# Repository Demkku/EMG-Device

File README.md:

Everything done, everything up to date and project presented.

final presentation:
https://docs.google.com/presentation/d/1xxOuLbYDE3mbfAP0H2NyMZXC_jU_autwXX0Ozza_mss/edit?usp=sharing

repository:
https://github.com/Demkku/EMG-Device

diary:
https://demkku.github.io/EMG-Device/

## Summary report

click [here]({{ site.baseurl }}/assets/EMG summary report.pdf) to download the summary report PDF with pictures and links
Note! link only available when browsing github pages and the link doesn't seem to work with Edge Browser

Our final concept was to measure heart rate using voltage sensors that have been amplified and filtered using operational amplifiers. Then the heart rate peak is detected with Arduino and the time difference between the peaks is measured and converted for a servo. Then the servo moves a needle on a measuring table to display the heart rate.

Our project consists of 4 elements: a circuit board and a case for it, a measuring table and software to read sensor data and convert into readable data and software to control a servo for the measuring table. 

Johannes designed the circuit board using KiCad. Voltage -sensors didn’t have strong enough signal, so in order to use it properly the signal had to be amplified and filtered using operational amplifiers. The voltage difference in the order of 1mV is measured across the chest with EKG electrodes, +, - and ground. The signal to an instrumental operational amplifier, where common mode noise is rejected, and the signal is amplified. Next, the signal goes through low and high pass filters. After filtering is further amplification and full wave rectification. Last, one more amplifier and then the signal goes to the ADC of ATMEGA328p. 

The case was designed by using Blender. Blender isn’t quite the best software in designing real life objects, but to create a simple and aesthetically nice case wasn’t a problem. The case was designed around the project images exported from Kicad. Some approximation by eye had to be made with components and they were pretty much correct. Only the size of the PCB would have gone terribly wrong if only the Kicad images were followed. The case was finally printed with Fortus 380mc printer. The result was fair, only the bottom was so thin that it cracked a little.

The measuring table was designed with Blender, from which the vector file was imported to Inkscape.
From Inkscape the vector file was exported as a pdf and then printed using a laser cutter out of plywood. The first cut table was too thick, and the servo couldn’t be put through. The arrow needed a hole for the screw, too. That’s why the table was cut again, and it turned out without problems. The servo was glued on the backside of the table.

The software was done on Arduino IDE platform. We programmed our code to ATMEGA328p microcontroller using Arduino UNO. The programs purpose was to measure the time difference between every heartbeat and calculate how many times the heart beats in a minute. EKG -sensors had a triangle wave that measured voltage of the heartbeat and it had some noise in it. To get reliable data we had to calculate the time difference between every peak of the voltage signal and not take the noise into account. We made the program to measure only the rising side of the wave and its maximum voltage. That way we got the most reliable data. Then we had to program a correct angle to a servo to display the heartrate on a measuring table.

Lessons learned 

We learned a lot in this project. We learned to use different software like KiCad, Blender, GitHub and Inkscape. We learned that one should always make a second version of the hardware design if any problems would rise. We learned how to use operational amplifiers in practice and how to compare different components to get the best one for its use. We also learned to watch carefully that everything gets correctly imported other software like all of our parts in the circuit board design didn’t get correctly imported to the drilling machine because we used KiCad as our design system.

We learned a good lesson in time management. It would be a lot better to divide the work of the project to entire period so there wouldn’t be such a rush at the end of the period to get everything done.

Our recommendation to others doing the same project is to take your time designing every element of the project carefully so everything goes smoothly when you start building up the project. This project can be a bit difficult so it would be better done in your on pace and not in an introductory course like Principles of digital fabrication.

Feedback to course responsibles

 The course was nice. It was good change for our usual courses that are heavily theoretic besed. It helped us to learn new things to designour projects so the course was also quite usefull.

## W19

On monday the case is printed, also
project software created and completed as it is very simple. 
The case slightly cracked during removal from the printer.

With the completetion of SW with Aruino IDE and receiving of the mesuring electrodes on the last minute
PROJECT COMPLETED!!!

the complete project:

testing after pads finally received:

The code:

## W18

Testing software created. Extensive testing and simulation done. 
See baseband testing report and oscilloscope pictures.

final output to ADC on simulation, massive hf noise:

Component values changed and filtering added

## W17

The remaining components soldered and measurements taken to the case.
During the soldering, some missing traces noticed, but fixed with jump wires.
Traces missing on the layout.

EKG electrodes ordered from Medkit.

Modeling of the case started with blender.
Also, modeling of the measuring table started with blender.

## W16

Midterm meeting

Later on the week, components received and first soldered.

## W15

The idea maybe changed to a heart rate sensor, which can be measured with the same circuit. 
Will be tested when components received, probably on W16 or 17

V2 board Milled with Success!!!

On the left first try, on the right the V2 board

Components ordered from Mouser.

Design for an enclosure started, will be 3D printed.

## W14

Layout V1 started and completed:

BOM completed.

V1 board milled. The board failed with board width at 0.4mm and uneven board at milling machine.
As a result wire width doubled to 0.8mm wherever possible.

## W13

After brainstorming requrements set

Kicad schematics started:

Kicad schematics done after a lot of reading about op amps:

## W12

The repositery and site created

## Start of the project:

Introductory report, EMG-Device

521159P Principles of Digital Fabrication 
DIGIFAB10 

The idea is to build a device that can measure EMG signal. EMG signals are created when muscles are used, and nerve impulses are sent. Impulses create a potential difference in the order of 1-10mV which is amplified, filtered and read with an Arduino. To meet course requirements an enclosure will be 3D printed and something laser cut. We arrived at the idea of an EMG device as a combination interest to the subject of bio signals, the challenge and courses about op amps are running in parallel with this course, so we can use in practice what we have learned. 

Other project that we thought of was an Arduino tank that could locate WIFI signal sources, but this would have been very software heavy, and because we are EE students, we wanted to put emphasis on hardware. Also locating sources turns out to be very hard. Our back up plan is an EKG device, which instead of 3 measuring lanes, uses only one.

BOM:
QTY	Component type	Package	Source	Price(eur)	URL

10	0.1uF capacitor	1206	Electronics club	0	

1	1uF capacitor	0603	Johannes	0	

1	12nF capacitor	0603	Johannes	0	

1	20nF capacitor	0603	Johannes	0	

3	47uF capacitor	5x5mm	Johannes	0	

1	47pF capacitor	0603	Johannes	0	

2	10uF tant. Cap.	1206?	Electronics club	0	

2	SMD LED	0603	Johannes	0	

2	1N4148W-F, SMD diode	SOD-123	Mouser	0,3	https://www.mouser.fi/ProductDetail/Diodes-Incorporated/1N4148W-7-F?qs=sGAEpiMZZMvilazpv%252bFqvbevgE8TPEOt

1	3 pin header	male 100mil header	Electronics club	0	

1	3 screw terminal	5mm terminal	Johannes	0	

1	2 screw terminal	5mm terminal	Johannes	0	

2	1MOhm resistor	0603?	Electronics club/Johannes	0	

1	470 Ohm resistor	0603	Johannes	0	

2	82kOhm resistor	0603	Johannes	0	

2	120kOhm resistor	0603	Johannes	0	

5	10kOhm resistor	0603	Johannes	0	

1	4,7kOhm resistor	0603	Johannes	0	

5	1kOhm resistor	0603	Johannes	0	

1	0 Ohm resistor	0603	Johannes	0	

1	15kOhm resistor	0603	Johannes	0	

1	100kOhm resistor	0603	Johannes	0	

2	DIP8 socket	DIP8	Johannes	0	

1	DIP14 socket	DIP14	Johannes	0	

1	DIP28 socket	DIP28	Johannes	0	

1	MAX1720 charge pump	TSOP-6	Mouser	0,58	https://www.mouser.fi/ProductDetail/ON-Semiconductor/MAX1720EUTG?qs=sGAEpiMZZMtitjHzVIkrqdfdkrf0Qy0Qzg%252b1DRXikVE%3d

1	HC-05 BT unit	custom	Johannes	0	

1	INA121PA inst. amp.	DIP8	Mouser	4,94	https://www.mouser.fi/ProductDetail/Texas-Instruments/INA121PA?qs=sGAEpiMZZMsE1dKaA2ImUPh%2fgv48%2feoeALcGDSe487k%3d

1	TL072IP op. Amp.	DIP8	Mouser	0,56	https://www.mouser.fi/ProductDetail/Texas-Instruments/TL072IP?qs=5BZzbFV4k2v7IBrcArRPQw==

1	LM324N	DIP14	Mouser	0,43	https://www.mouser.fi/ProductDetail/Texas-Instruments/LM324N?qs=sGAEpiMZZMtCHixnSjNA6Araa3jp4DVB37ZJv3RooEc%3d

1	ATMega 328p	DIP28	Electronics club	0	

1	LM1117 3.3V regulator	TO252	Electronics club	0	

8	button things	button	Johannes	0	

50	Electrodes, 34mm	button	Medkit.fi	14,26	https://www.medkit.fi/ambu-blue-sensor-m-oo-s?___store=finland&nosto=frontpage-nosto-1

## Welcome to GitHub Pages

You can use the [editor on GitHub](https://github.com/Demkku/EMG-Device/edit/master/README.md) to maintain and preview the content for your website in Markdown files.

Whenever you commit to this repository, GitHub Pages will run [Jekyll](https://jekyllrb.com/) to rebuild the pages in your site, from the content in your Markdown files.

### Markdown

Markdown is a lightweight and easy-to-use syntax for styling your writing. It includes conventions for

```markdown
Syntax highlighted code block

# Header 1
## Header 2
### Header 3

- Bulleted
- List

1. Numbered
2. List

**Bold** and _Italic_ and `Code` text

[Link](url) and 
```

For more details see [GitHub Flavored Markdown](https://guides.github.com/features/mastering-markdown/).

### Jekyll Themes

Your Pages site will use the layout and styles from the Jekyll theme you have selected in your [repository settings](https://github.com/Demkku/EMG-Device/settings). The name of this theme is saved in the Jekyll `_config.yml` configuration file.

### Support or Contact

Having trouble with Pages? Check out our [documentation](https://help.github.com/categories/github-pages-basics/) or [contact support](https://github.com/contact) and we’ll help you sort it out.

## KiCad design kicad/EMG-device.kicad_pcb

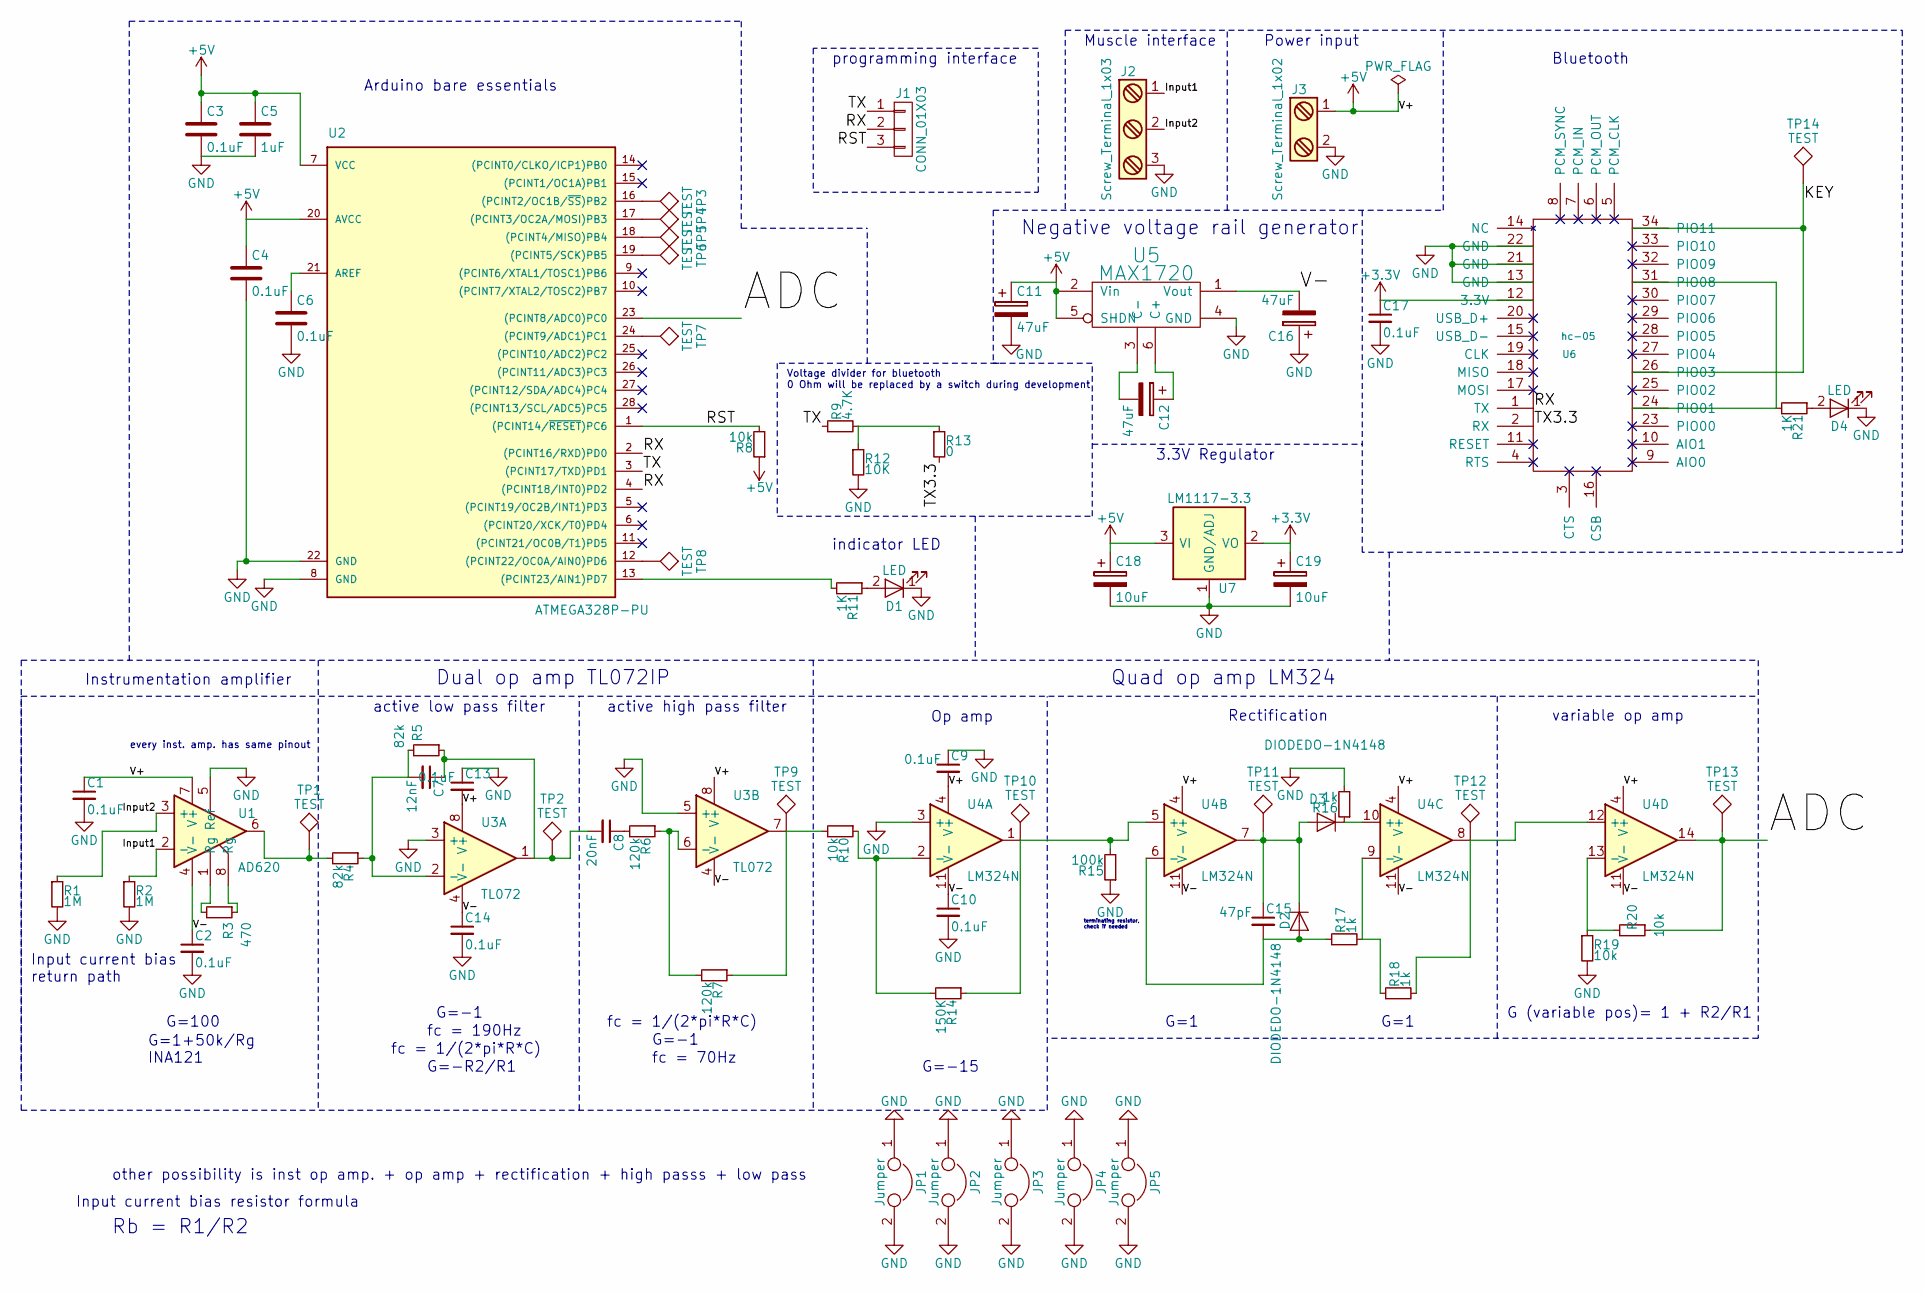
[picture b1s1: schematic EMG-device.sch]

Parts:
C1, C2, C3, C4, C6, C9, C10, C13, C14, C17: 0.1uF; C_1206_HandSoldering
C5: 1uF; C_0603_HandSoldering
C7: 12nF; C_0603_HandSoldering
C8: 20nF; C_0603_HandSoldering
C11, C12, C16: 47uF; CP_Elec_5x5.3
C15: 47pF; C_0603_HandSoldering
C18, C19: 10uF; CP_Tantalum_Case-U_EIA-6032-15_Hand
D1, D4: LED; LED_0603_HandSoldering
D2, D3: DIODEDO-1N4148; SOD-123
J1: CONN_01X03; Pin_Header_Straight_1x03_Pitch2.54mm
J2: Screw_Terminal_1x03; TerminalBlock_Altech_AK300-3_P5.00mm
J3: Screw_Terminal_1x02; TerminalBlock_Altech_AK300-2_P5.00mm
JP1, JP2, JP3, JP4: Jumper; WireConnection_2.00mmDrill
JP5: Jumper; SolderWirePad_2x_1mmDrill
R1, R2: 1M; R_0603_HandSoldering
R3: 470; R_0603_HandSoldering
R4, R5: 82k; R_0603_HandSoldering
R6, R7: 120k; R_0603_HandSoldering
R8, R10, R19, R20: 10k; R_0603_HandSoldering
R9: 4.7K; R_0603_HandSoldering
R11, R21: 1K; R_0603_HandSoldering
R12: 10K; R_0603_HandSoldering
R13: 0; R_0603_HandSoldering
R14: 150K; R_0603_HandSoldering
R15: 100k; R_0603_HandSoldering
R16, R17, R18: 1k; R_0603_HandSoldering
TP1, TP2, TP3, TP4, TP5, TP6, TP7, TP8, TP9, TP10, TP11, TP12, TP13, TP14: TEST; Measurement_Point_Round-SMD-Pad_Big
U1: AD620; DIP-8_W7.62mm_Socket
U2: ATMEGA328P-PU; DIP-28_W7.62mm_Socket
U3: TL072; DIP-8_W7.62mm_Socket
U4: LM324N; DIP-14_W7.62mm_Socket
U5: MAX1720; TSOP-6_1.65x3.05mm_Pitch0.95mm
U6: hc-05; HC-05
U7: LM1117-3.3; TO-252-3_TabPin2

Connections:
+3V3: C17.1, C19.1, U6.12 (3.3V), U7.2 (VO), U7.4 (VO)
+5V: C1.1, C3.1, C4.1, C5.1, C9.2, C11.1, C13.2, C18.1, J3.1, R8.1, U1.7 (V+), U2.7 (VCC), U2.20 (AVCC), U3.8 (V+), U4.4 (V+), U5.2 (Vin), U5.5 (SHDN), U7.3 (VI)
/ADC: R20.1, TP13.1, U2.23 ((PCINT8/ADC0)PC0), U4.14
/Input1: J2.1, R2.1, U1.2 (-)
/Input2: J2.2, R1.1, U1.3 (+)
/KEY: TP14.1, U6.26 (PIO03), U6.34 (PIO11)
/RST: J1.3, R8.2, U2.1 ((PCINT14/~RESET~)PC6)
/RX: J1.2, U2.2 ((PCINT16/RXD)PD0), U2.4 ((PCINT18/INT0)PD2), U6.1 (TX)
/TX: J1.1, R9.1, U2.3 ((PCINT17/TXD)PD1)
/TX3.3: R13.2, U6.2 (RX)
/V-: C2.1, C10.1, C14.1, C16.2, U1.4 (V-), U3.4 (V-), U4.11 (V-), U5.1 (Vout)
GND: C1.2, C2.2, C3.2, C4.2, C5.2, C6.2, C9.1, C10.2, C11.2, C13.1, C14.2, C16.1, C17.2, C18.2, C19.2, D1.1 (K), D4.1 (K), J2.3, J3.2, JP1.1, JP1.2, JP2.1, JP2.2, JP3.1, JP3.2, JP4.1, JP4.2, JP5.1, JP5.2, R1.2, R2.2, R12.2, R15.1, R16.2, R19.2, U1.5 (Ref), U2.8 (GND), U2.22 (GND), U3.3 (+), U3.5 (+), U4.3 (+), U5.4 (GND), U6.13 (GND), U6.21 (GND), U6.22 (GND), U7.1 (GND/ADJ)
unnamed: C6.1, U2.21 (AREF)
unnamed: C7.1, C8.2, R5.1, TP2.1, U3.1
unnamed: C7.2, R4.1, R5.2, U3.2 (-)
unnamed: C8.1, R6.2
unnamed: C12.1, U5.6 (C+)
unnamed: C12.2, U5.3 (C-)
unnamed: C15.1, D2.C, D3.A, TP11.1, U4.7
unnamed: C15.2, D2.A, R17.1, U4.6 (-)
unnamed: D1.2 (A), R11.1
unnamed: D3.C, R16.1, U4.10 (+)
unnamed: D4.2 (A), R21.1
unnamed: R3.1, U1.8 (Rg)
unnamed: R3.2, U1.1 (Rg)
unnamed: R4.2, TP1.1, U1.6
unnamed: R6.1, R7.2, U3.6 (-)
unnamed: R10.1, R14.2, U4.2 (-)
unnamed: R7.1, R10.2, TP9.1, U3.7
unnamed: R11.2, U2.13 ((PCINT23/AIN1)PD7)
unnamed: R9.2, R12.1, R13.1
unnamed: R14.1, R15.2, TP10.1, U4.1, U4.5 (+)
unnamed: R17.2, R18.1, U4.9 (-)
unnamed: R18.2, TP12.1, U4.8, U4.12 (+)
unnamed: R19.1, R20.2, U4.13 (-)
unnamed: R21.2, U6.24 (PIO01), U6.31 (PIO08)
unnamed: TP3.1, U2.16 ((PCINT2/OC1B/~SS~)PB2)
unnamed: TP4.1, U2.17 ((PCINT3/OC2A/MOSI)PB3)
unnamed: TP5.1, U2.18 ((PCINT4/MISO)PB4)
unnamed: TP6.1, U2.19 ((PCINT5/SCK)PB5)
unnamed: TP7.1, U2.24 ((PCINT9/ADC1)PC1)
unnamed: TP8.1, U2.12 ((PCINT22/OC0A/AIN0)PD6)

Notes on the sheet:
Arduino bare essentials
programming interface
Bluetooth
Voltage divider for bluetooth 0 Ohm will be replaced by a switch during development
indicator LED
Instrumentation amplifier
every inst. amp. has same pinout
Muscle interface
Op amp
active high pass filter
Quad op amp LM324
Rectification
active low pass filter
Dual op amp TL072IP
variable op amp
terminating resistor, check if needed
Power input
Negative voltage rail generator
Rb = R1/R2
Input current bias return path
fc = 1/(2*pi*R*C)
G=-1
fc = 70Hz
G=100
G=-15
G=1
G=-1
fc = 190Hz
other possibility is inst op amp. + op amp + rectification + high passs + low pass
G (variable pos)= 1 + R2/R1
Input current bias resistor formula
G=1+50k/Rg INA121
G=-R2/R1
3.3V Regulator

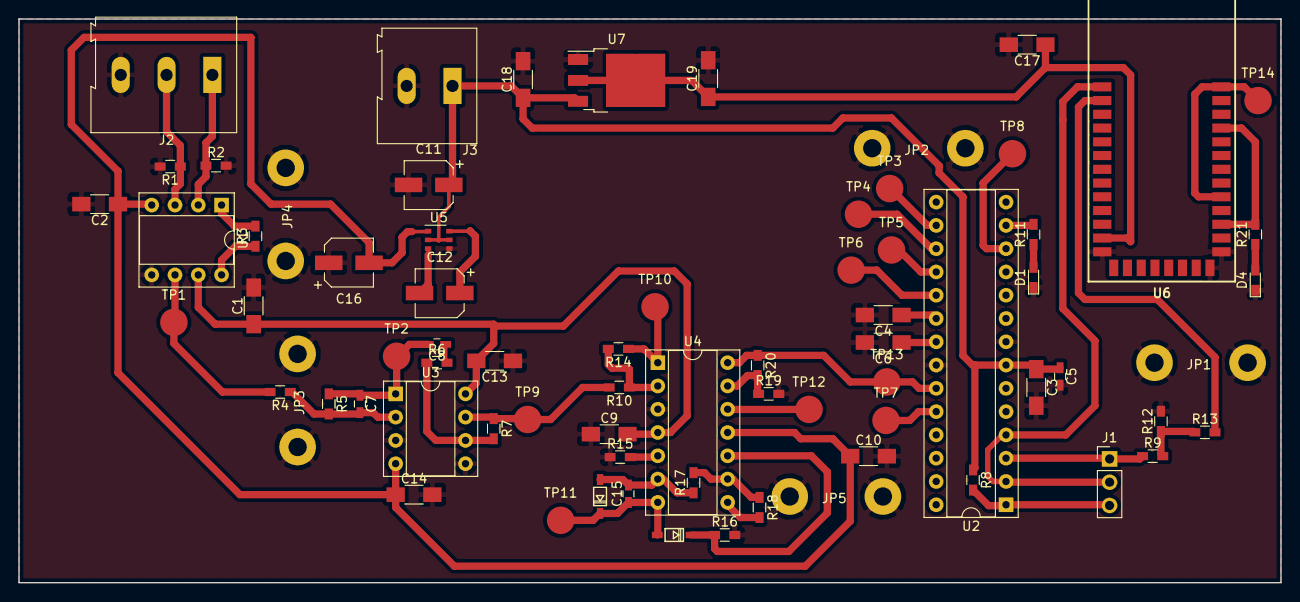
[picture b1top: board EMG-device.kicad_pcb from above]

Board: 2 copper layers, 137.7 x 61.5 mm, 73 parts (0 on the bottom side), 42 nets.

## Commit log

2018-03-22 Set theme jekyll-theme-minimal
2018-03-22 New site
2018-03-30 files created
    files created
2018-03-30 Moved files, schematic V1 done
2018-03-31 input bias resistor document
2018-03-31 schematics done
    schematics 1.0 done
    BOM updated, but not ready
2018-04-02 BOM done, added missing components to schematics, added footpints
2018-04-02 layout done, some changes in schematics
2018-04-04 wires xhanged to 0.8mil
2018-04-06 layout wires increased in size
2018-04-15 intro report, more pictures
2018-05-08 final adjustments
2018-05-08 pictures to be added
2018-05-08 Mechanics added
2018-05-08 SW added
2018-05-09 pictures
2018-05-09 more pictures
2018-05-11 final report
